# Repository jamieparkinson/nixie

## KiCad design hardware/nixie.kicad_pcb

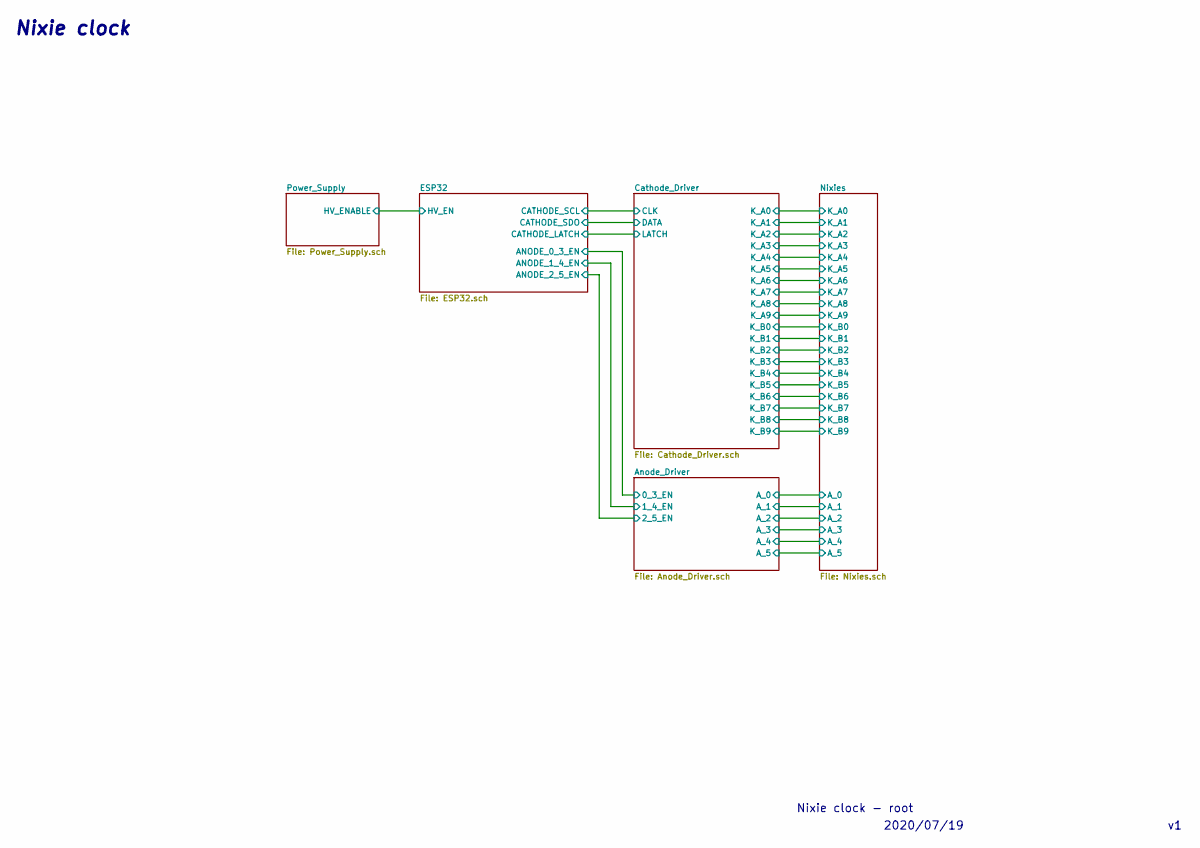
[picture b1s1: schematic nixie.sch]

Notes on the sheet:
Nixie clock - root
2020/07/19
Nixie clock

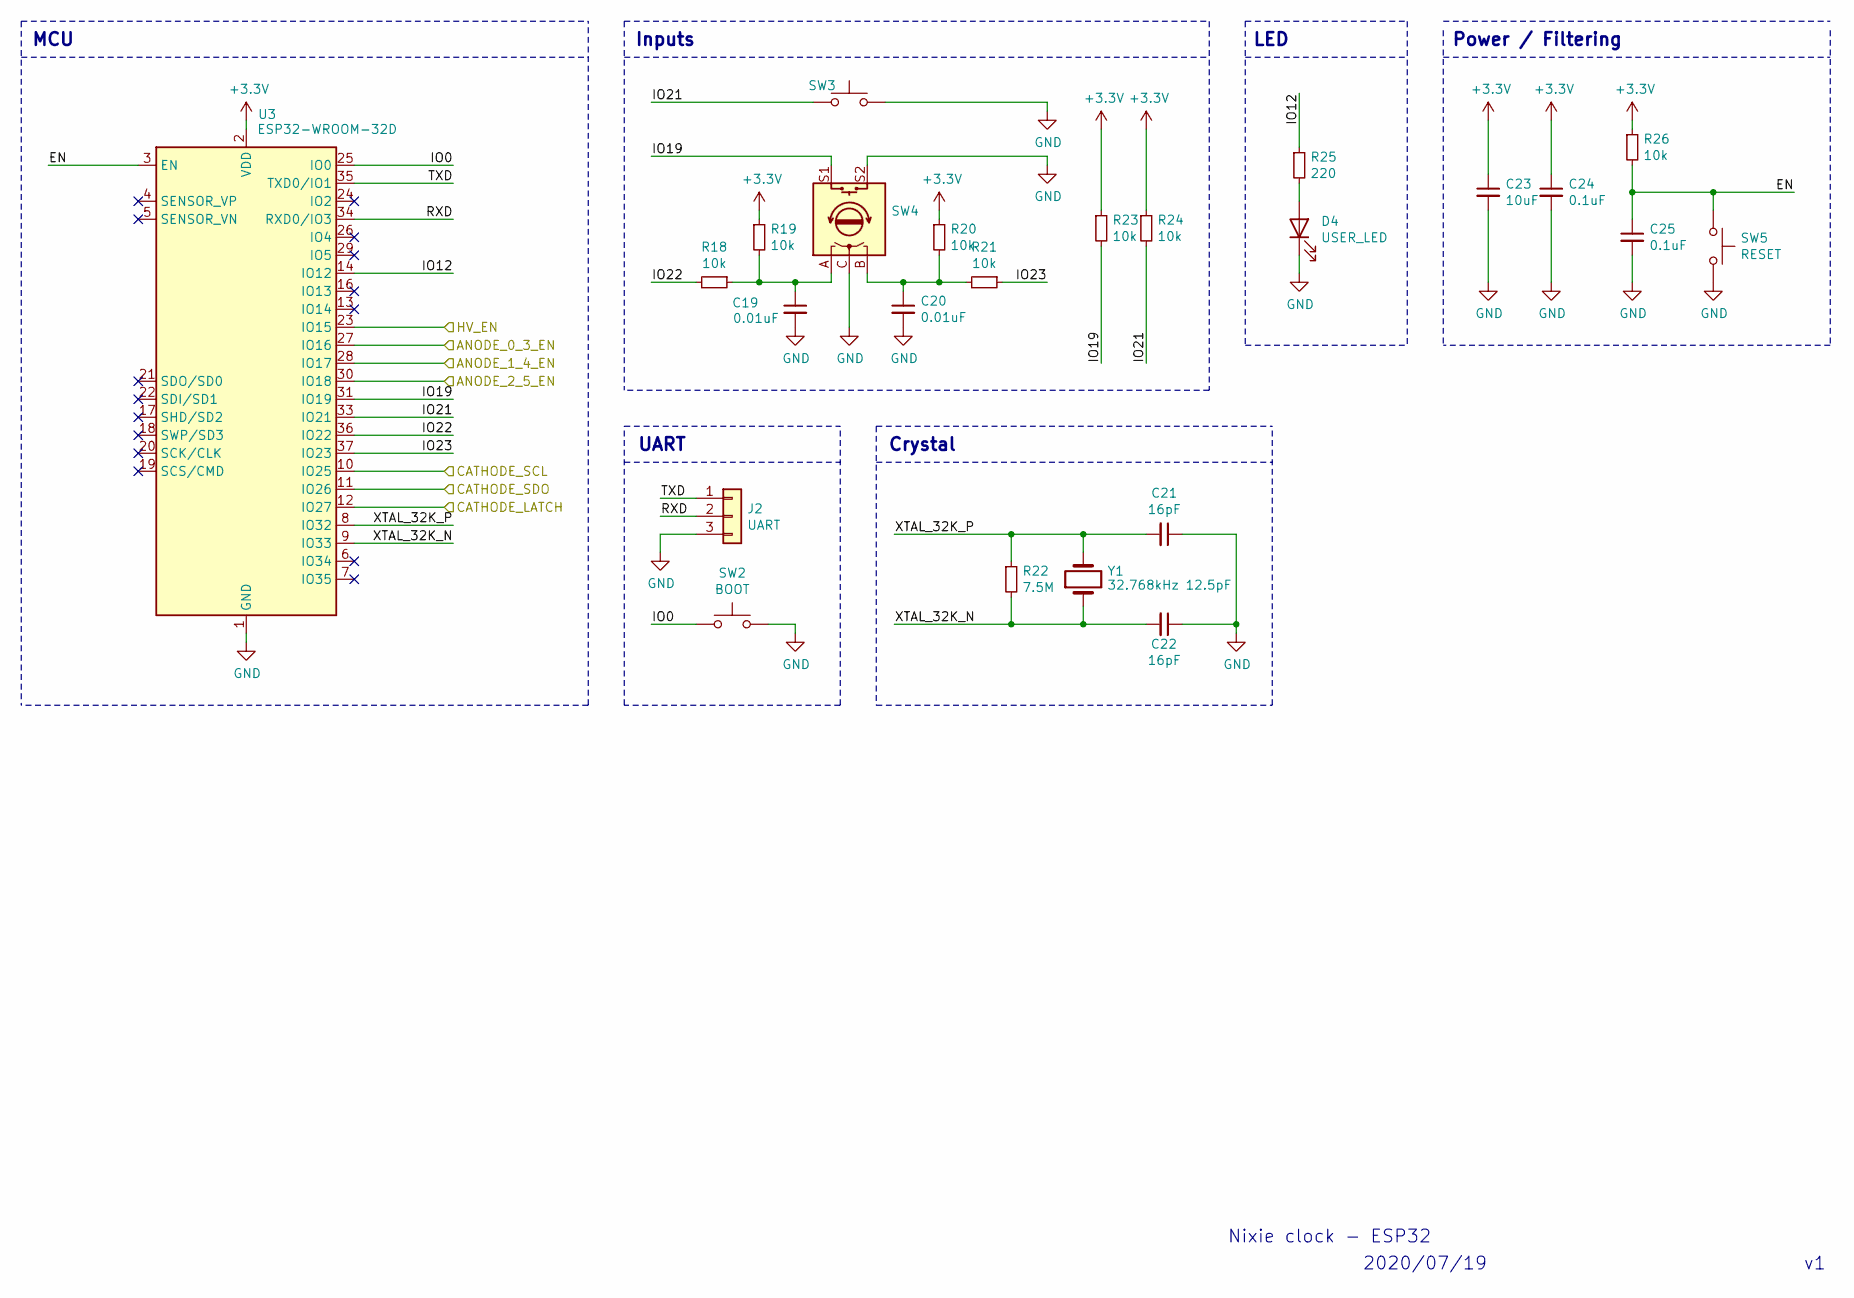
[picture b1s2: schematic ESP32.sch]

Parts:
C19, C20: 0.01uF; C_0603_1608Metric
C21, C22: 16pF; C_0603_1608Metric
C23: 10uF; C_0603_1608Metric
C24, C25: 0.1uF; C_0603_1608Metric
D4: USER_LED; LED_0805_2012Metric
J2: UART; PinHeader_1x03_P2.54mm_Horizontal
R18, R19, R20, R21, R23, R24, R26: 10k; R_0603_1608Metric
R22: 7.5M; R_0603_1608Metric
R25: 220; R_0603_1608Metric
SW2: BOOT; SW_Push_1P1T-SH_NO_CK_KMR2xxG
SW3: USER_BUT1; Switch_CK_D6
SW4: Rotary Encoder; RotaryEncoder_Alps_EC12E-Switch_Vertical_H20mm
SW5: RESET; SW_Push_1P1T-SH_NO_CK_KMR2xxG
U3: ESP32-WROOM-32D; ESP32-WROOM-32
Y1: 32.768kHz 12.5pF; XTAL_LFXTAL003000

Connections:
+3V3: C23.1, C24.1, R19.1, R20.1, R23.1, R24.1, R26.1, U3.2 (VDD); also elsewhere on the board
/Anode_Driver/0_3_EN: U3.27 (IO16); also elsewhere on the board
/Anode_Driver/1_4_EN: U3.28 (IO17); also elsewhere on the board
/Anode_Driver/2_5_EN: U3.30 (IO18); also elsewhere on the board
/ESP32/CATHODE_LATCH: U3.12 (IO27); also elsewhere on the board
/ESP32/CATHODE_SCL: U3.10 (IO25); also elsewhere on the board
/ESP32/CATHODE_SDO: U3.11 (IO26); also elsewhere on the board
/ESP32/EN: C25.1, R26.2, SW5.1, U3.3 (EN)
/ESP32/HV_EN: U3.23 (IO15); also elsewhere on the board
/ESP32/IO0: SW2.1, U3.25 (IO0)
/ESP32/IO12: R25.1, U3.14 (IO12)
/ESP32/IO19: R23.2, SW4.S1, U3.31 (IO19)
/ESP32/IO21: R24.2, SW3.1, U3.33 (IO21)
/ESP32/IO22: R18.2, U3.36 (IO22)
/ESP32/IO23: R21.1, U3.37 (IO23)
/ESP32/RXD: J2.2, U3.34 (RXD0/IO3)
/ESP32/TXD: J2.1, U3.35 (TXD0/IO1)
/ESP32/XTAL_32K_N: C22.2, R22.2, U3.9 (IO33), Y1.1
/ESP32/XTAL_32K_P: C21.2, R22.1, U3.8 (IO32), Y1.2
GND: C19.2, C20.2, C21.1, C22.1, C23.2, C24.2, C25.2, D4.1 (K), J2.3, SW2.2, SW3.2, SW4.C, SW4.S2, SW5.2, U3.1 (GND), U3.15 (GND), U3.38 (GND), U3.39 (GND); also elsewhere on the board
unnamed: C19.1, R18.1, R19.2, SW4.A
unnamed: C20.1, R20.2, R21.2, SW4.B
unnamed: D4.2 (A), R25.2

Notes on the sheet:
MCU
Power / Filtering
Crystal
LED
UART
Nixie clock - ESP32
2020/07/19
Inputs

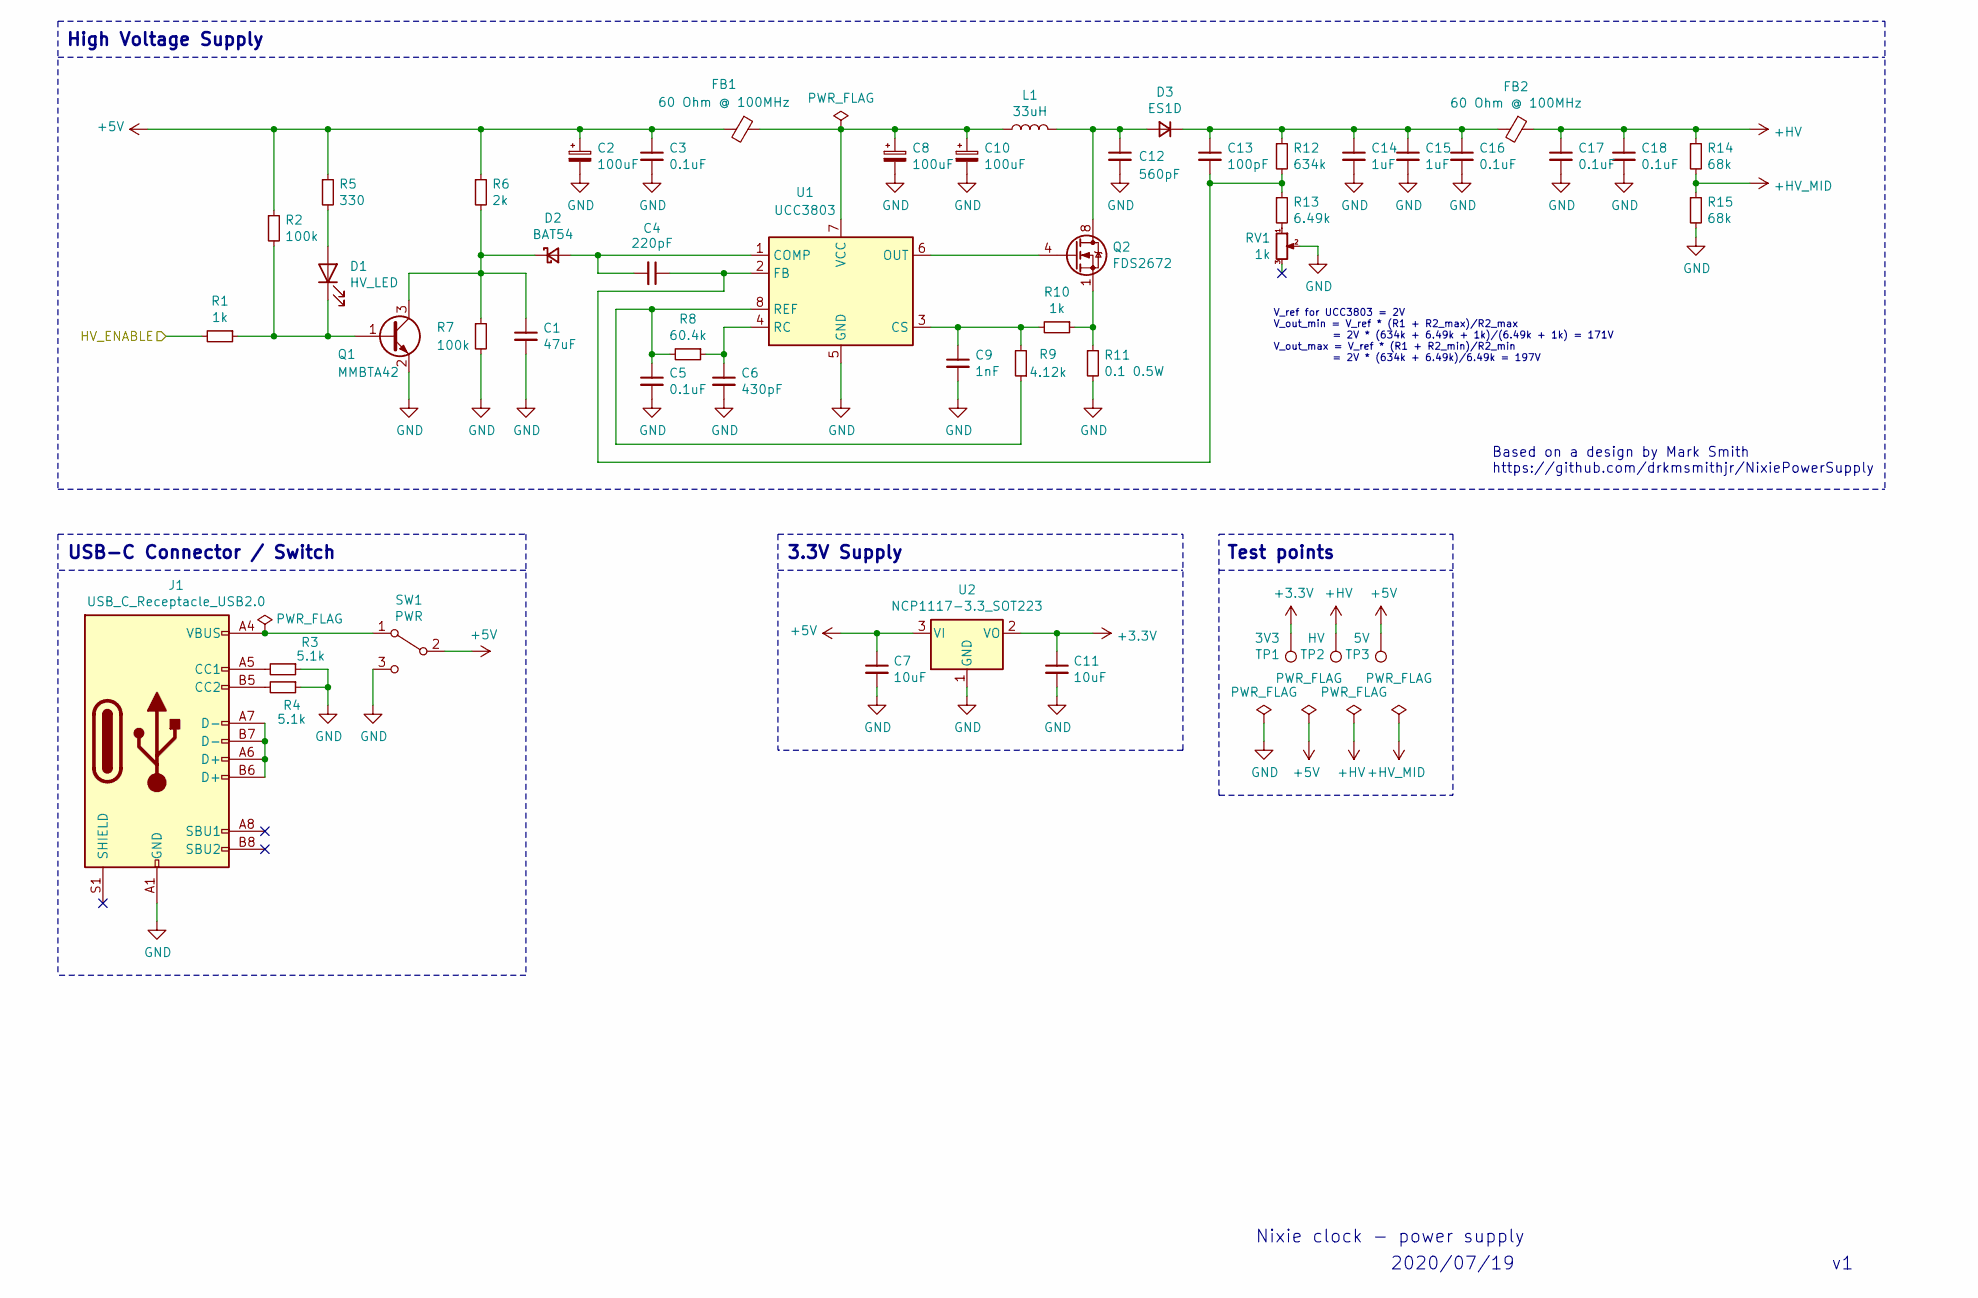
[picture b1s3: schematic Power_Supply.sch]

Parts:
C1: 47uF; C_0603_1608Metric
C2, C8, C10: 100uF; CP_Elec_5x5.4
C3, C5, C16, C17, C18: 0.1uF; C_0603_1608Metric
C4: 220pF; C_0603_1608Metric
C6: 430pF; C_0603_1608Metric
C7, C11: 10uF; C_0603_1608Metric
C9: 1nF; C_0603_1608Metric
C12: 560pF; C_0603_1608Metric
C13: 100pF; C_0603_1608Metric
C14, C15: 1uF; C_0603_1608Metric
D1: HV_LED; LED_0805_2012Metric
D2: BAT54; D_SOT-23_ANK
D3: ES1D; D_SMA_Handsoldering
FB1, FB2: 60 Ohm @ 100MHz; L_0603_1608Metric
J1: USB_C_Receptacle_USB2.0; WURTH_632723100011
L1: 33uH; L_12x12mm_H8mm
Q1: MMBTA42; SOT-23
Q2: FDS2672; SOIC-8_3.9x4.9mm_P1.27mm
R1, R10: 1k; R_0603_1608Metric
R2, R7: 100k; R_0603_1608Metric
R3, R4: 5.1k; R_0603_1608Metric
R5: 330; R_0603_1608Metric
R6: 2k; R_0603_1608Metric
R8: 60.4k; R_0603_1608Metric
R9: 4.12k; R_0603_1608Metric
R11: 0.1 0.5W; R_1210_3225Metric
R12: 634k; R_0603_1608Metric
R13: 6.49k; R_0603_1608Metric
R14, R15: 68k; R_0603_1608Metric
RV1: 1k; Potentiometer_Bourns_3314G_Vertical
SW1: PWR; SW_SPDT_CK-JS102011SAQN
TP1: 3V3; TestPoint_Pad_D2.0mm
TP2: HV; TestPoint_Pad_D2.0mm
TP3: 5V; TestPoint_Pad_D2.0mm
U1: UCC3803; SOIC-8_3.9x4.9mm_P1.27mm
U2: NCP1117-3.3_SOT223; SOT-223-3_TabPin2

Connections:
+3V3: C11.1, TP1.1, U2.2 (VO); also elsewhere on the board
+5V: C2.1, C3.1, C7.1, FB1.2, R2.1, R5.1, R6.1, SW1.2 (B), TP3.1, U2.3 (VI)
+HV: C17.1, C18.1, FB2.1, R14.1, TP2.1; also elsewhere on the board
+HV_MID: R14.2, R15.1; also elsewhere on the board
/ESP32/HV_EN: R1.2; also elsewhere on the board
GND: C1.2, C2.2, C3.2, C5.2, C6.2, C7.2, C8.2, C9.2, C10.2, C11.2, C12.2, C14.2, C15.2, C16.2, C17.2, C18.2, J1.A1 (GND), J1.A12 (GND), J1.B1 (GND), J1.B12 (GND), Q1.2 (E), R3.1, R4.1, R7.2, R11.2, R15.2, RV1.2, SW1.3 (C), U1.5 (GND), U2.1 (GND); also elsewhere on the board
unnamed: C1.1, D2.1 (K), Q1.3 (C), R6.2, R7.1
unnamed: C4.2, D2.2 (A), U1.1 (COMP)
unnamed: C5.1, R8.2, R9.1, U1.8 (REF)
unnamed: C6.1, R8.1, U1.4 (RC)
unnamed: C9.1, R9.2, R10.2, U1.3 (CS)
unnamed: C8.1, C10.1, FB1.1, L1.1, U1.7 (VCC)
unnamed: C12.1, D3.2 (A), L1.2, Q2.5 (D), Q2.6 (D), Q2.7 (D), Q2.8 (D)
unnamed: C13.1, C14.1, C15.1, C16.1, D3.1 (K), FB2.2, R12.1
unnamed: C4.1, C13.2, R12.2, R13.1, U1.2 (FB)
unnamed: D1.1 (K), Q1.1 (B), R1.1, R2.2
unnamed: D1.2 (A), R5.2
unnamed: J1.A4 (VBUS), J1.A9 (VBUS), J1.B4 (VBUS), J1.B9 (VBUS), SW1.1 (A)
unnamed: J1.A5 (CC1), R3.2
unnamed: J1.A6 (D+), J1.A7 (D-), J1.B6 (D+), J1.B7 (D-)
unnamed: J1.B5 (CC2), R4.2
unnamed: Q2.1 (S), Q2.2 (S), Q2.3 (S), R10.1, R11.1
unnamed: Q2.4 (G), U1.6 (OUT)
unnamed: R13.2, RV1.1

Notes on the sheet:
USB-C Connector / Switch
3.3V Supply
Test points
High Voltage Supply
Nixie clock - power supply
2020/07/19
V_ref for UCC3803 = 2V V_out_min = V_ref * (R1 + R2_max)/R2_max = 2V * (634k + 6.49k + 1k)/(6.49k + 1k) = 171V V_out_max = V_ref * (R1 + R2_min)/R2_min = 2V * (634k + 6.49k)/6.49k = 197V
Based on a design by Mark Smith https://github.com/drkmsmithjr/NixiePowerSupply

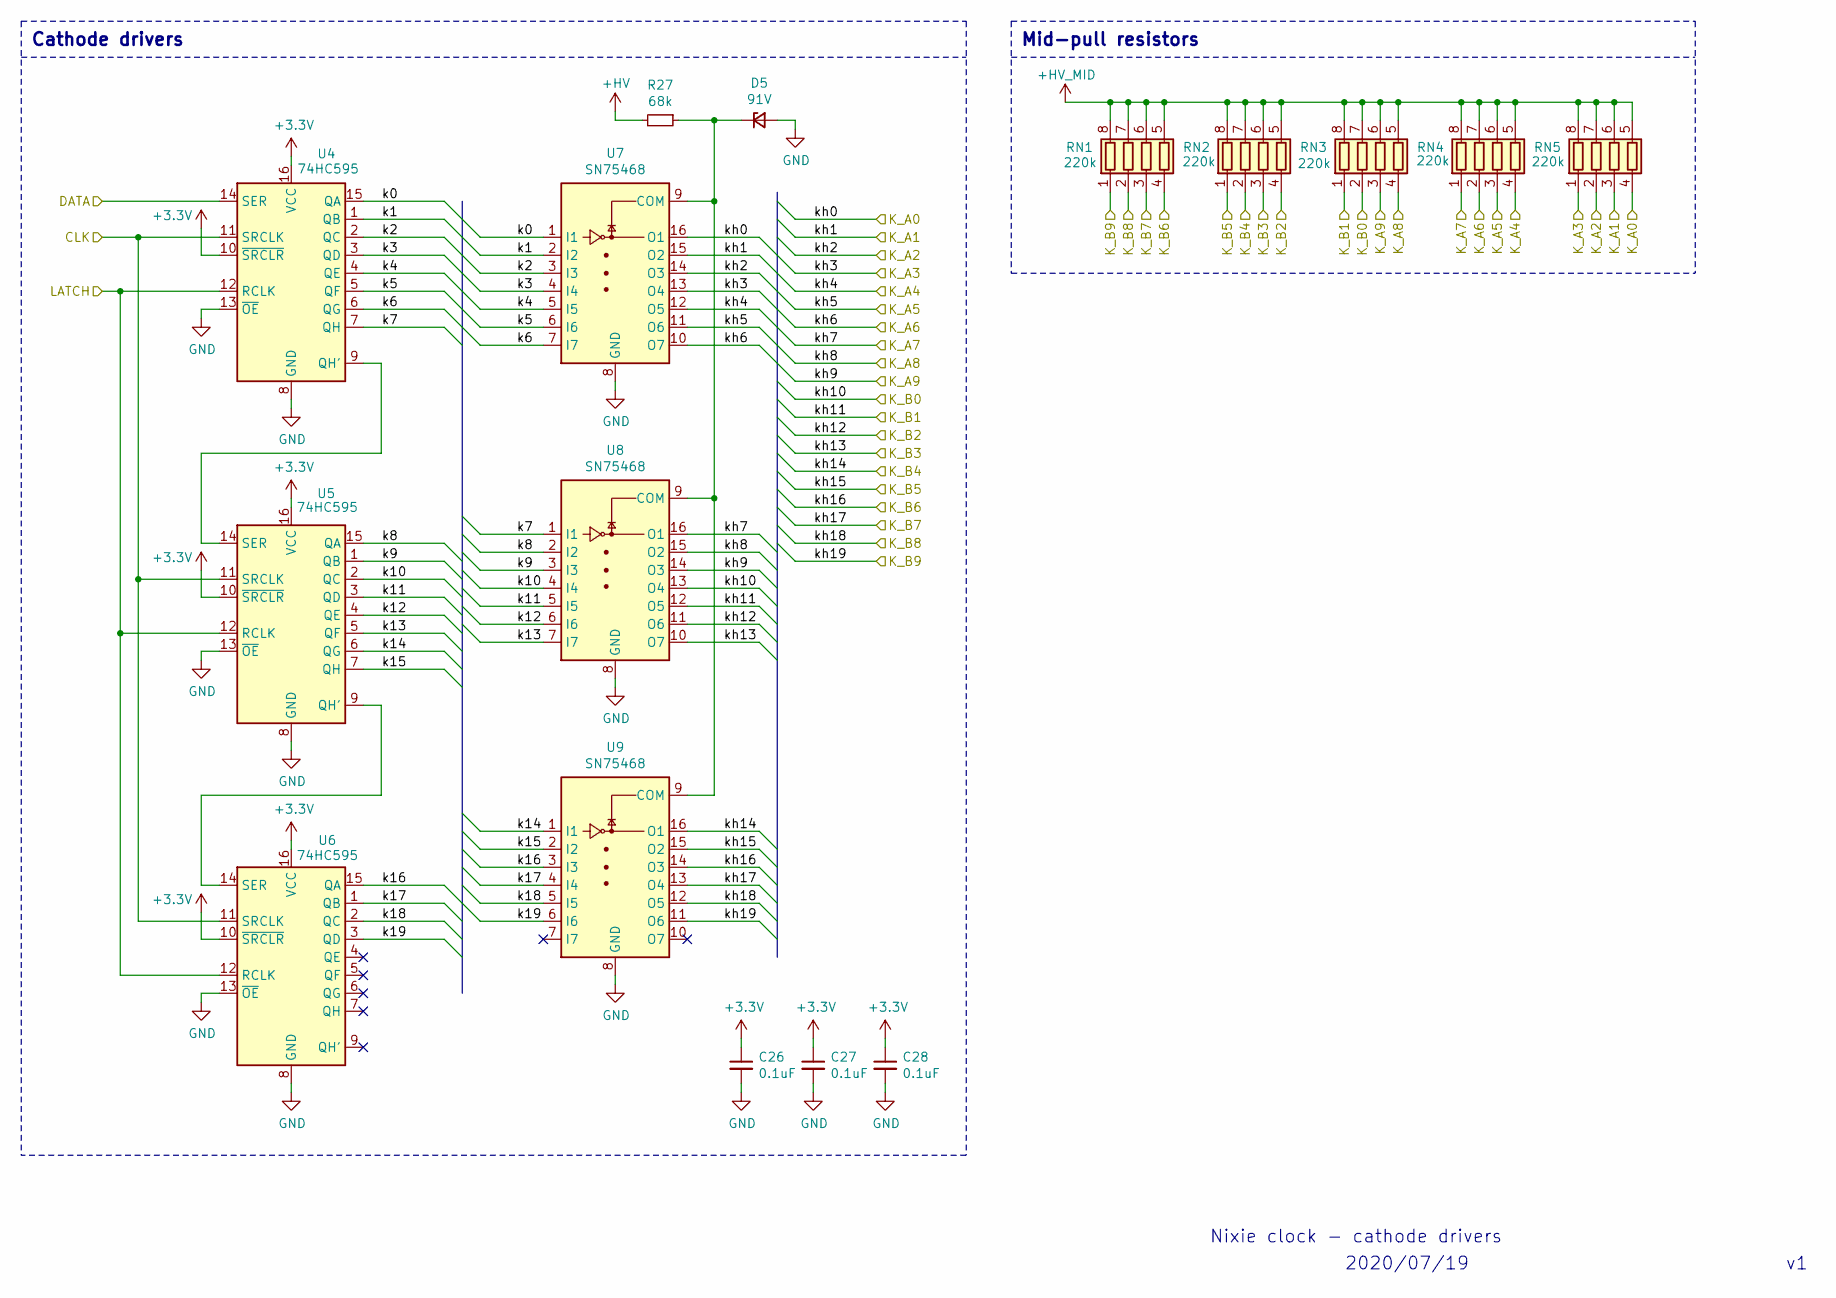
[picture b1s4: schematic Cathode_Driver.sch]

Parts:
C26, C27, C28: 0.1uF; C_0603_1608Metric
D5: 91V; D_SOD-123
R27: 68k; R_0603_1608Metric
RN1, RN2, RN3, RN4, RN5: 220k; R_Array_Convex_4x1206
U4, U5, U6: 74HC595; SOIC-16_3.9x9.9mm_P1.27mm
U7, U8, U9: SN75468; SOIC-16_3.9x9.9mm_P1.27mm

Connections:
+3V3: C26.1, C27.1, C28.1, U4.10 (~SRCLR), U4.16 (VCC), U5.10 (~SRCLR), U5.16 (VCC), U6.10 (~SRCLR), U6.16 (VCC); also elsewhere on the board
+HV: R27.2; also elsewhere on the board
+HV_MID: RN1.5 (R4.2), RN1.6 (R3.2), RN1.7 (R2.2), RN1.8 (R1.2), RN2.5 (R4.2), RN2.6 (R3.2), RN2.7 (R2.2), RN2.8 (R1.2), RN3.5 (R4.2), RN3.6 (R3.2), RN3.7 (R2.2), RN3.8 (R1.2), RN4.5 (R4.2), RN4.6 (R3.2), RN4.7 (R2.2), RN4.8 (R1.2), RN5.5 (R4.2), RN5.6 (R3.2), RN5.7 (R2.2), RN5.8 (R1.2); also elsewhere on the board
/Cathode_Driver/K_A0: RN5.4 (R4.1), U7.16 (O1); also elsewhere on the board
/Cathode_Driver/K_A1: RN5.3 (R3.1), U7.15 (O2); also elsewhere on the board
/Cathode_Driver/K_A2: RN5.2 (R2.1), U7.14 (O3); also elsewhere on the board
/Cathode_Driver/K_A3: RN5.1 (R1.1), U7.13 (O4); also elsewhere on the board
/Cathode_Driver/K_A4: RN4.4 (R4.1), U7.12 (O5); also elsewhere on the board
/Cathode_Driver/K_A5: RN4.3 (R3.1), U7.11 (O6); also elsewhere on the board
/Cathode_Driver/K_A6: RN4.2 (R2.1), U7.10 (O7); also elsewhere on the board
/Cathode_Driver/K_A7: RN4.1 (R1.1), U8.16 (O1); also elsewhere on the board
/Cathode_Driver/K_A8: RN3.4 (R4.1), U8.15 (O2); also elsewhere on the board
/Cathode_Driver/K_A9: RN3.3 (R3.1), U8.14 (O3); also elsewhere on the board
/Cathode_Driver/K_B0: RN3.2 (R2.1), U8.13 (O4); also elsewhere on the board
/Cathode_Driver/K_B1: RN3.1 (R1.1), U8.12 (O5); also elsewhere on the board
/Cathode_Driver/K_B2: RN2.4 (R4.1), U8.11 (O6); also elsewhere on the board
/Cathode_Driver/K_B3: RN2.3 (R3.1), U8.10 (O7); also elsewhere on the board
/Cathode_Driver/K_B4: RN2.2 (R2.1), U9.16 (O1); also elsewhere on the board
/Cathode_Driver/K_B5: RN2.1 (R1.1), U9.15 (O2); also elsewhere on the board
/Cathode_Driver/K_B6: RN1.4 (R4.1), U9.14 (O3); also elsewhere on the board
/Cathode_Driver/K_B7: RN1.3 (R3.1), U9.13 (O4); also elsewhere on the board
/Cathode_Driver/K_B8: RN1.2 (R2.1), U9.12 (O5); also elsewhere on the board
/Cathode_Driver/K_B9: RN1.1 (R1.1), U9.11 (O6); also elsewhere on the board
/Cathode_Driver/k0: U4.15 (QA), U7.1 (I1)
/Cathode_Driver/k1: U4.1 (QB), U7.2 (I2)
/Cathode_Driver/k2: U4.2 (QC), U7.3 (I3)
/Cathode_Driver/k3: U4.3 (QD), U7.4 (I4)
/Cathode_Driver/k4: U4.4 (QE), U7.5 (I5)
/Cathode_Driver/k5: U4.5 (QF), U7.6 (I6)
/Cathode_Driver/k6: U4.6 (QG), U7.7 (I7)
/Cathode_Driver/k7: U4.7 (QH), U8.1 (I1)
/Cathode_Driver/k8: U5.15 (QA), U8.2 (I2)
/Cathode_Driver/k9: U5.1 (QB), U8.3 (I3)
/Cathode_Driver/k10: U5.2 (QC), U8.4 (I4)
/Cathode_Driver/k11: U5.3 (QD), U8.5 (I5)
/Cathode_Driver/k12: U5.4 (QE), U8.6 (I6)
/Cathode_Driver/k13: U5.5 (QF), U8.7 (I7)
/Cathode_Driver/k14: U5.6 (QG), U9.1 (I1)
/Cathode_Driver/k15: U5.7 (QH), U9.2 (I2)
/Cathode_Driver/k16: U6.15 (QA), U9.3 (I3)
/Cathode_Driver/k17: U6.1 (QB), U9.4 (I4)
/Cathode_Driver/k18: U6.2 (QC), U9.5 (I5)
/Cathode_Driver/k19: U6.3 (QD), U9.6 (I6)
/ESP32/CATHODE_LATCH: U4.12 (RCLK), U5.12 (RCLK), U6.12 (RCLK); also elsewhere on the board
/ESP32/CATHODE_SCL: U4.11 (SRCLK), U5.11 (SRCLK), U6.11 (SRCLK); also elsewhere on the board
/ESP32/CATHODE_SDO: U4.14 (SER); also elsewhere on the board
GND: C26.2, C27.2, C28.2, D5.2 (A), U4.8 (GND), U4.13 (~OE), U5.8 (GND), U5.13 (~OE), U6.8 (GND), U6.13 (~OE), U7.8 (GND), U8.8 (GND), U9.8 (GND); also elsewhere on the board
unnamed: D5.1 (K), R27.1, U7.9 (COM), U8.9 (COM), U9.9 (COM)
unnamed: U4.9 (QH'), U5.14 (SER)
unnamed: U5.9 (QH'), U6.14 (SER)

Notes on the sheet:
Cathode drivers
Mid-pull resistors
Nixie clock - cathode drivers
2020/07/19

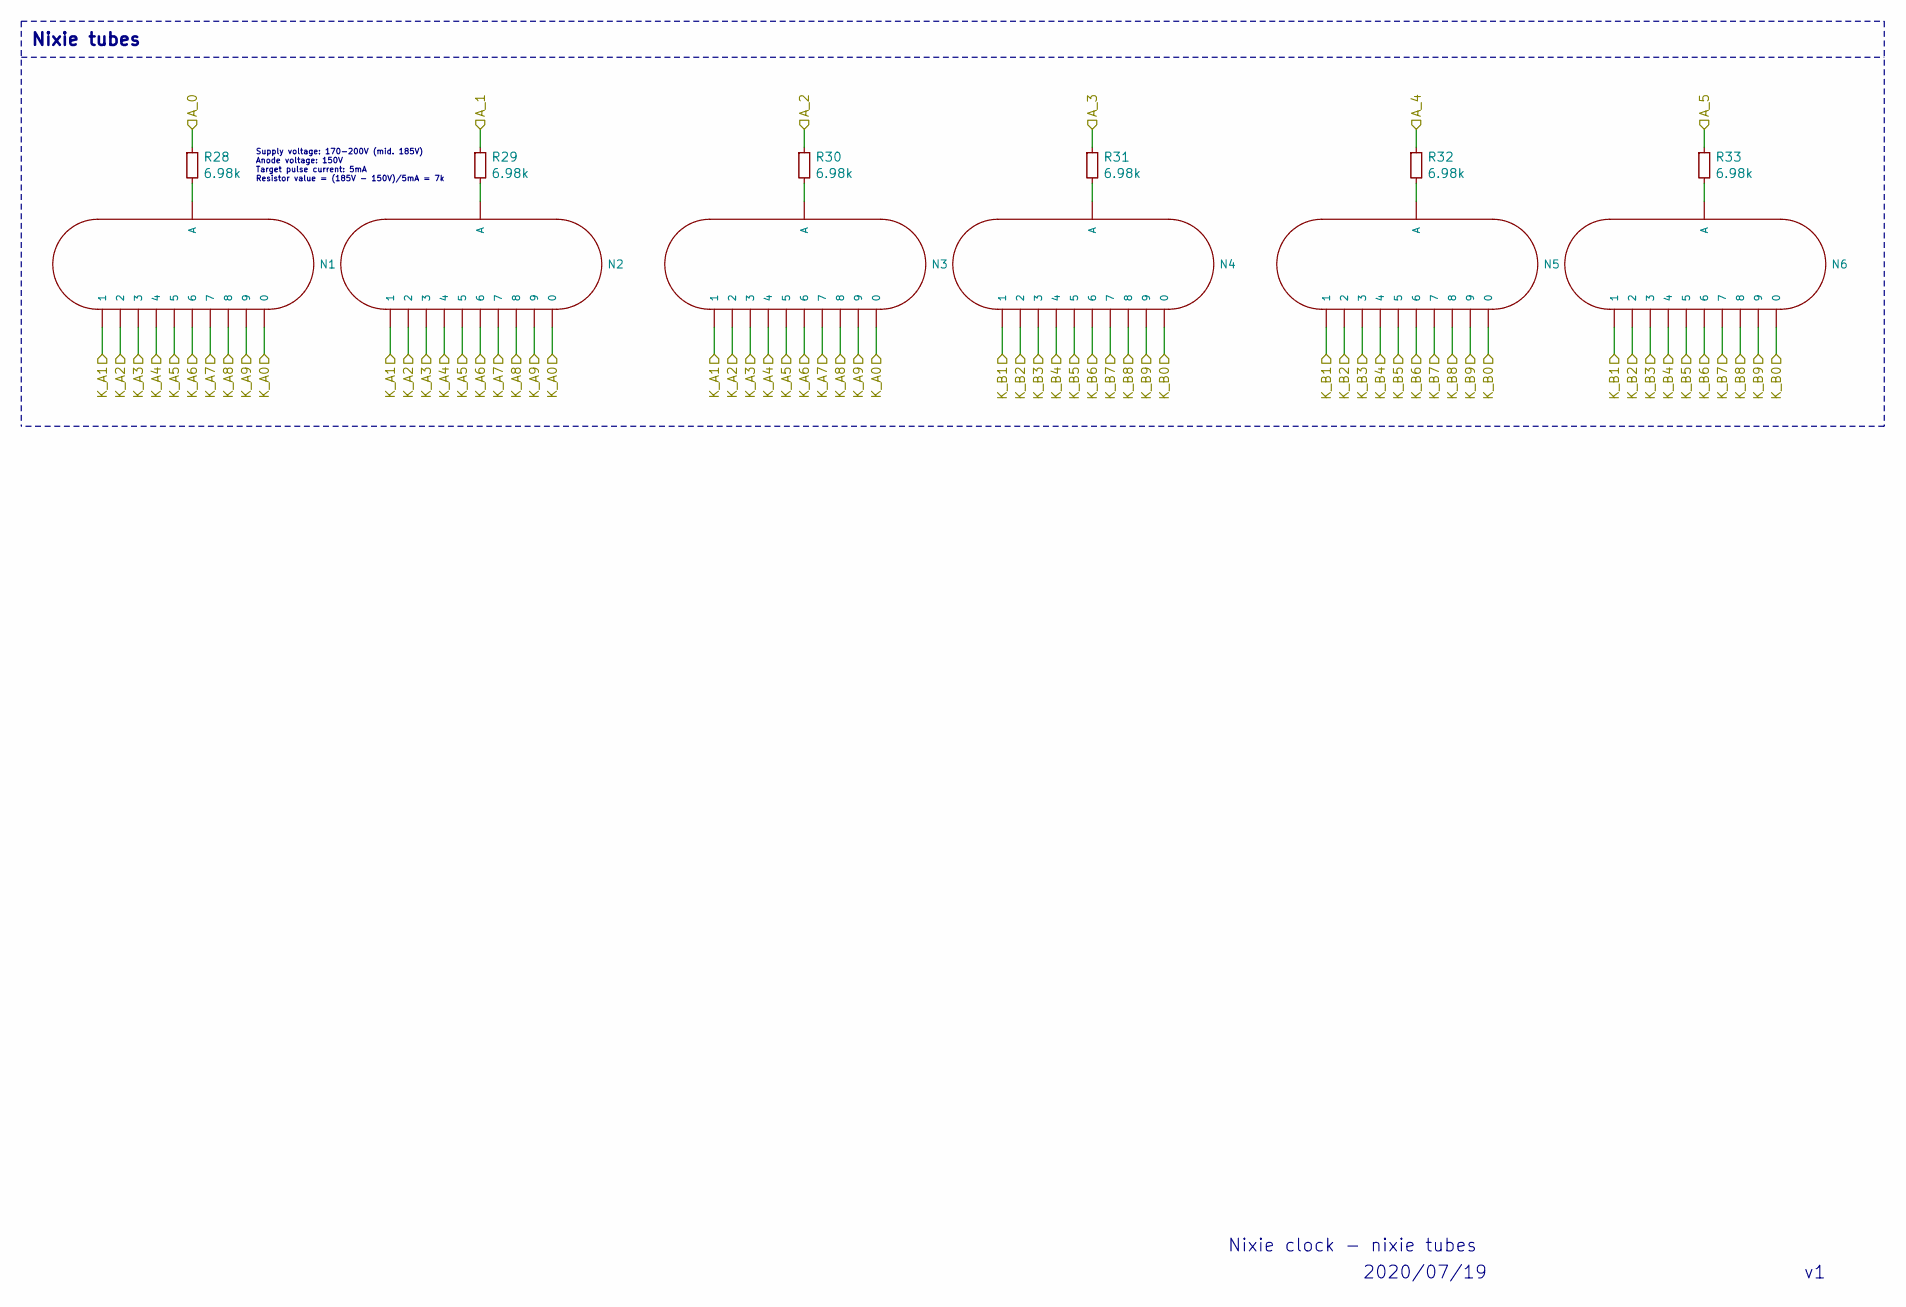
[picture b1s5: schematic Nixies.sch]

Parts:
N1, N2, N3, N4, N5, N6: IN-8; nixies-us-IN-8
R28, R29, R30, R31, R32, R33: 6.98k; R_0603_1608Metric

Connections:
/Anode_Driver/A_0: R28.1, R31.1; also elsewhere on the board
/Anode_Driver/A_1: R29.1, R32.1; also elsewhere on the board
/Anode_Driver/A_2: R30.1, R33.1; also elsewhere on the board
/Cathode_Driver/K_A0: N1.0, N2.0, N3.0; also elsewhere on the board
/Cathode_Driver/K_A1: N1.1, N2.1, N3.1; also elsewhere on the board
/Cathode_Driver/K_A2: N1.2, N2.2, N3.2; also elsewhere on the board
/Cathode_Driver/K_A3: N1.3, N2.3, N3.3; also elsewhere on the board
/Cathode_Driver/K_A4: N1.4, N2.4, N3.4; also elsewhere on the board
/Cathode_Driver/K_A5: N1.5, N2.5, N3.5; also elsewhere on the board
/Cathode_Driver/K_A6: N1.6, N2.6, N3.6; also elsewhere on the board
/Cathode_Driver/K_A7: N1.7, N2.7, N3.7; also elsewhere on the board
/Cathode_Driver/K_A8: N1.8, N2.8, N3.8; also elsewhere on the board
/Cathode_Driver/K_A9: N1.9, N2.9, N3.9; also elsewhere on the board
/Cathode_Driver/K_B0: N4.0, N5.0, N6.0; also elsewhere on the board
/Cathode_Driver/K_B1: N4.1, N5.1, N6.1; also elsewhere on the board
/Cathode_Driver/K_B2: N4.2, N5.2, N6.2; also elsewhere on the board
/Cathode_Driver/K_B3: N4.3, N5.3, N6.3; also elsewhere on the board
/Cathode_Driver/K_B4: N4.4, N5.4, N6.4; also elsewhere on the board
/Cathode_Driver/K_B5: N4.5, N5.5, N6.5; also elsewhere on the board
/Cathode_Driver/K_B6: N4.6, N5.6, N6.6; also elsewhere on the board
/Cathode_Driver/K_B7: N4.7, N5.7, N6.7; also elsewhere on the board
/Cathode_Driver/K_B8: N4.8, N5.8, N6.8; also elsewhere on the board
/Cathode_Driver/K_B9: N4.9, N5.9, N6.9; also elsewhere on the board
unnamed: N1.A, R28.2
unnamed: N2.A, R29.2
unnamed: N3.A, R30.2
unnamed: N4.A, R31.2
unnamed: N5.A, R32.2
unnamed: N6.A, R33.2

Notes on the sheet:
Nixie tubes
Nixie clock - nixie tubes
2020/07/19
Supply voltage: 170-200V (mid. 185V) Anode voltage: 150V Target pulse current: 5mA Resistor value = (185V - 150V)/5mA = 7k

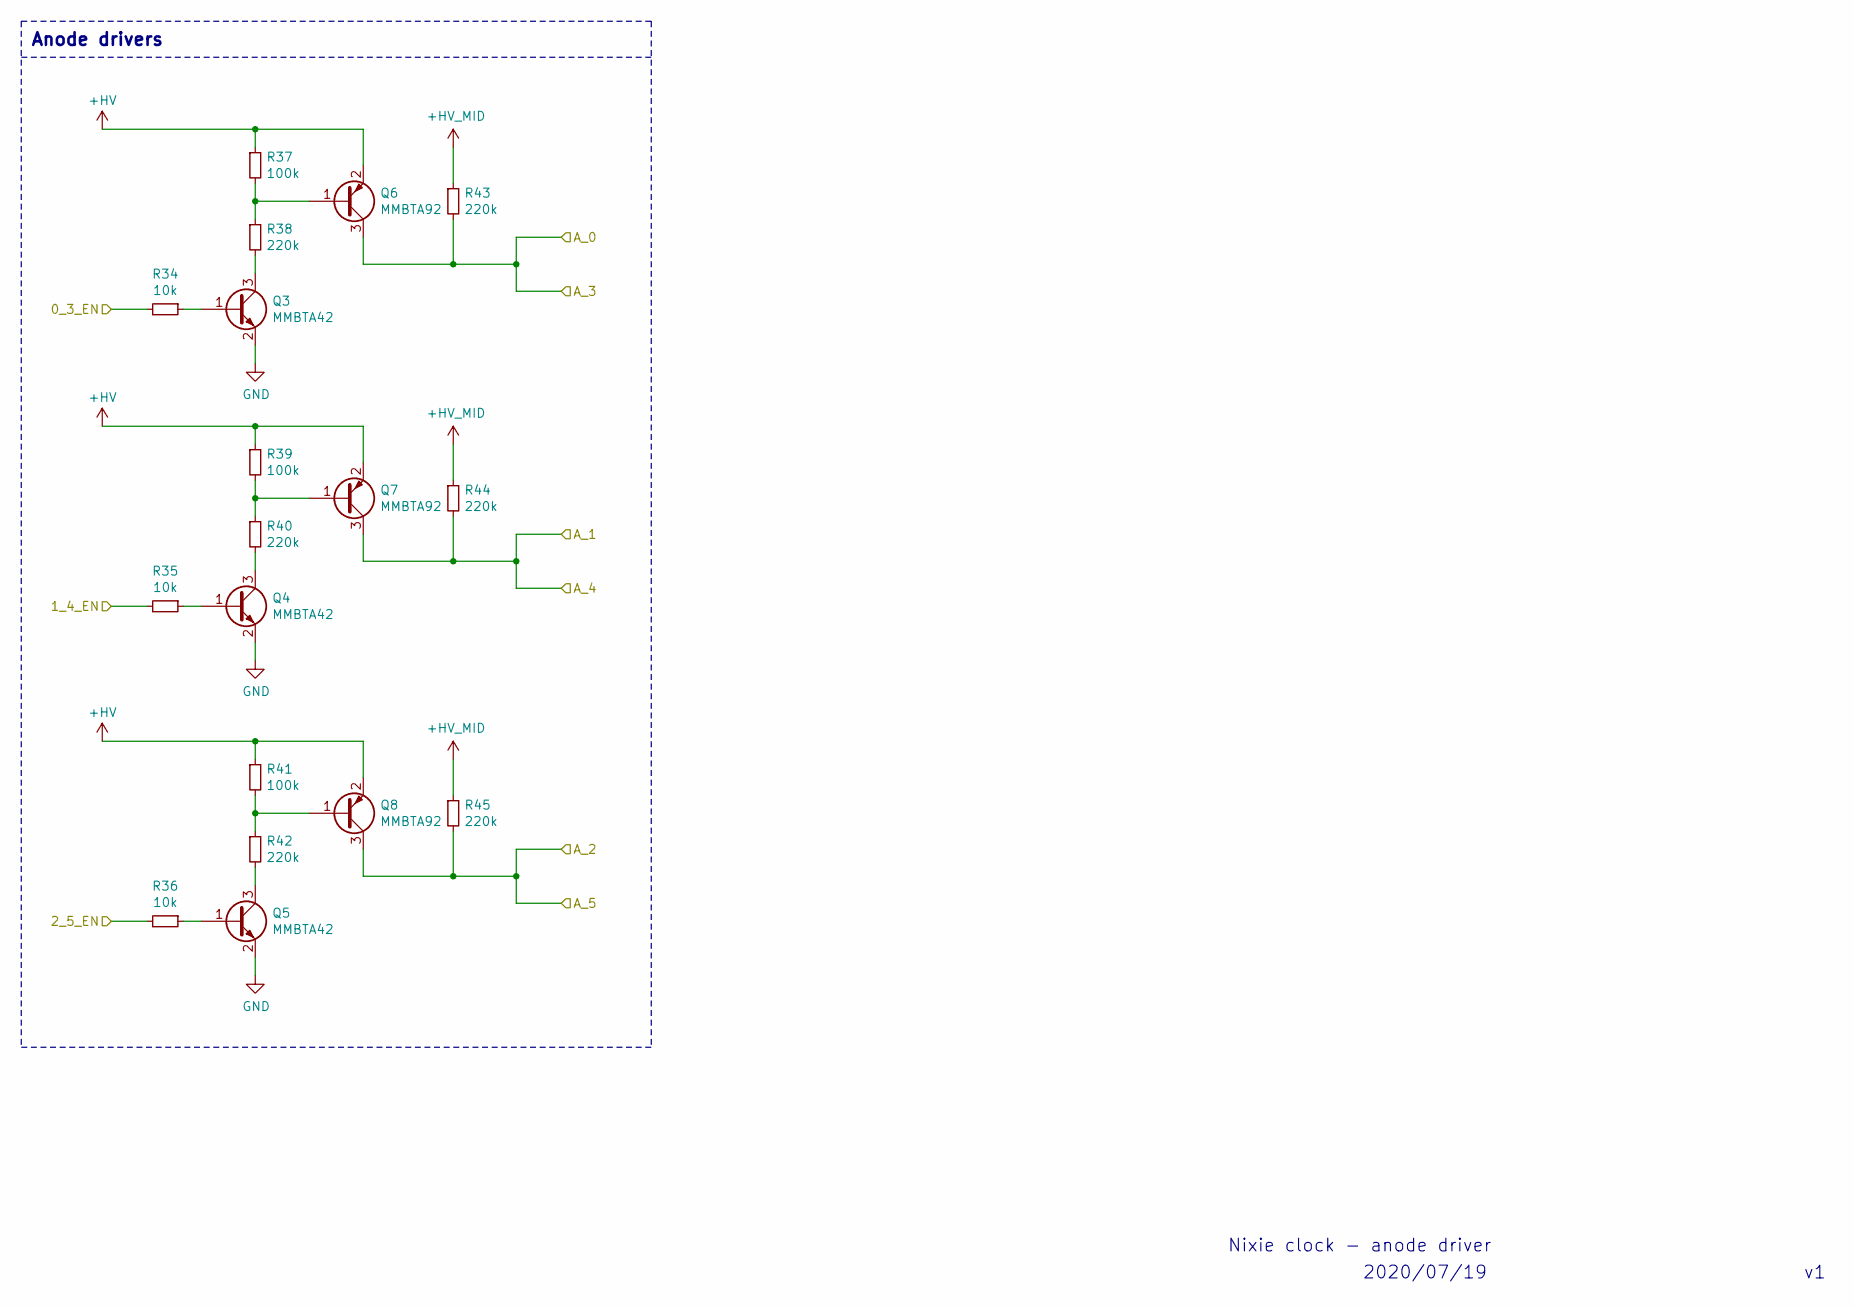
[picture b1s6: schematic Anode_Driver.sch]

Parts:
Q3, Q4, Q5: MMBTA42; SOT-23
Q6, Q7, Q8: MMBTA92; SOT-23
R34, R35, R36: 10k; R_0603_1608Metric
R37, R39, R41: 100k; R_0603_1608Metric
R38, R40, R42, R43, R44, R45: 220k; R_0603_1608Metric

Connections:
+HV: Q6.2 (E), Q7.2 (E), Q8.2 (E), R37.1, R39.1, R41.1; also elsewhere on the board
+HV_MID: R43.1, R44.1, R45.1; also elsewhere on the board
/Anode_Driver/0_3_EN: R34.2; also elsewhere on the board
/Anode_Driver/1_4_EN: R35.2; also elsewhere on the board
/Anode_Driver/2_5_EN: R36.2; also elsewhere on the board
/Anode_Driver/A_0: Q6.3 (C), R43.2; also elsewhere on the board
/Anode_Driver/A_1: Q7.3 (C), R44.2; also elsewhere on the board
/Anode_Driver/A_2: Q8.3 (C), R45.2; also elsewhere on the board
GND: Q3.2 (E), Q4.2 (E), Q5.2 (E); also elsewhere on the board
unnamed: Q3.1 (B), R34.1
unnamed: Q3.3 (C), R38.2
unnamed: Q4.1 (B), R35.1
unnamed: Q4.3 (C), R40.2
unnamed: Q5.1 (B), R36.1
unnamed: Q5.3 (C), R42.2
unnamed: Q6.1 (B), R37.2, R38.1
unnamed: Q7.1 (B), R39.2, R40.1
unnamed: Q8.1 (B), R41.2, R42.1

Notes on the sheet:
Anode drivers
Nixie clock - anode driver
2020/07/19

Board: 2 copper layers, 119 parts (0 on the bottom side), 105 nets, no tracks yet.

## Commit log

2020-07-25 Add v1 of schematic
2020-08-05 Replace 2 switches with a rotary encoder, other tweaks and annotations
2020-08-09 Create footprints and netlist
